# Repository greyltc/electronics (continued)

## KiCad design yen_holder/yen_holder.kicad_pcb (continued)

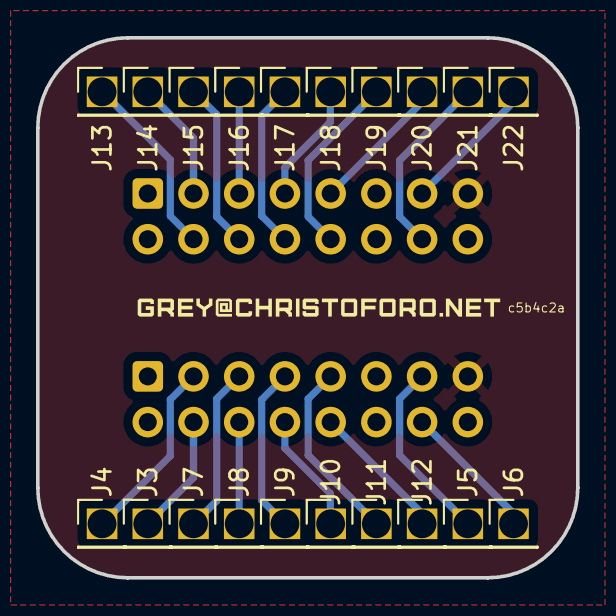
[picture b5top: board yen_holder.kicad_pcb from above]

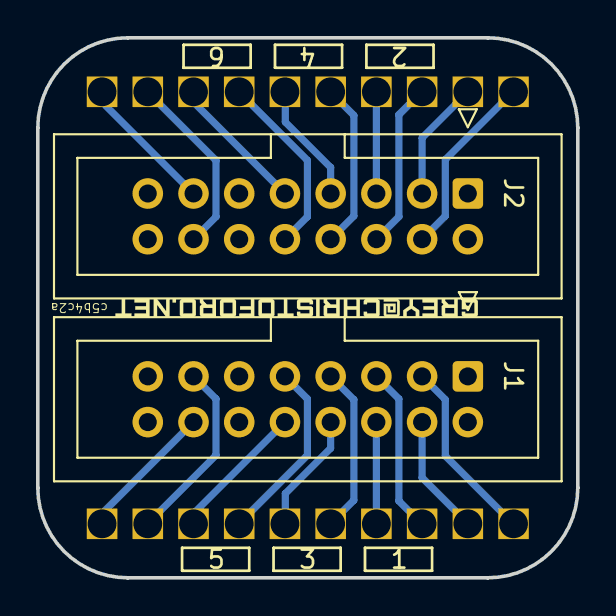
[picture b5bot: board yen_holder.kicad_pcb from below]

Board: 2 copper layers, 30.0 x 30.0 mm, 24 parts (3 on the bottom side), 21 nets.
